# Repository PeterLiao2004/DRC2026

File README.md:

# DRC2026 Autonomous Car

Autonomous car project using a Raspberry Pi 5 for high-level autonomy and a Raspberry Pi Pico for low-level motor control.

## Repository Layout

```text
DRC2026/
+-- pi5_software/       High-level autonomy, perception, planning, and Pi-side services
+-- pico_firmware/      Low-level motor, encoder, and safety firmware for the Raspberry Pi Pico
+-- PCB/                KiCad PCB project, footprints, symbols, and fabrication outputs
+-- interfaces/         Communication contracts between the Pi 5, Pico, and hardware
+-- docs/               System architecture, bring-up notes, and design decisions
```

## System Roles

- **Raspberry Pi 5:** Main computer for camera processing, navigation, decision making, logging, and sending drive commands.
- **Raspberry Pi Pico:** Real-time controller for motors, encoders, watchdogs, and low-level safety behavior.
- **PCB:** Custom carrier/control board that connects power, Pico, motor driver, encoders, and expansion headers.

## Suggested Development Flow

1. Define or update the Pi-to-Pico protocol in `interfaces/`.
2. Implement low-level behavior in `pico_firmware/` and test it on the bench.
3. Implement high-level autonomy in `pi5_software/` against the same protocol.
4. Capture wiring, power, and bring-up notes in `docs/`.
5. Keep PCB source files and generated fabrication outputs in `PCB/`.

## Bring-Up Checklist

- Confirm PCB power rails before connecting the Pi 5 or Pico.
- Flash Pico firmware and verify motor disable/stop behavior first.
- Verify encoder telemetry with the car lifted off the ground.
- Connect Pi 5 software to the Pico protocol and test low-speed commands.
- Add autonomy features only after manual command and safety paths are reliable.

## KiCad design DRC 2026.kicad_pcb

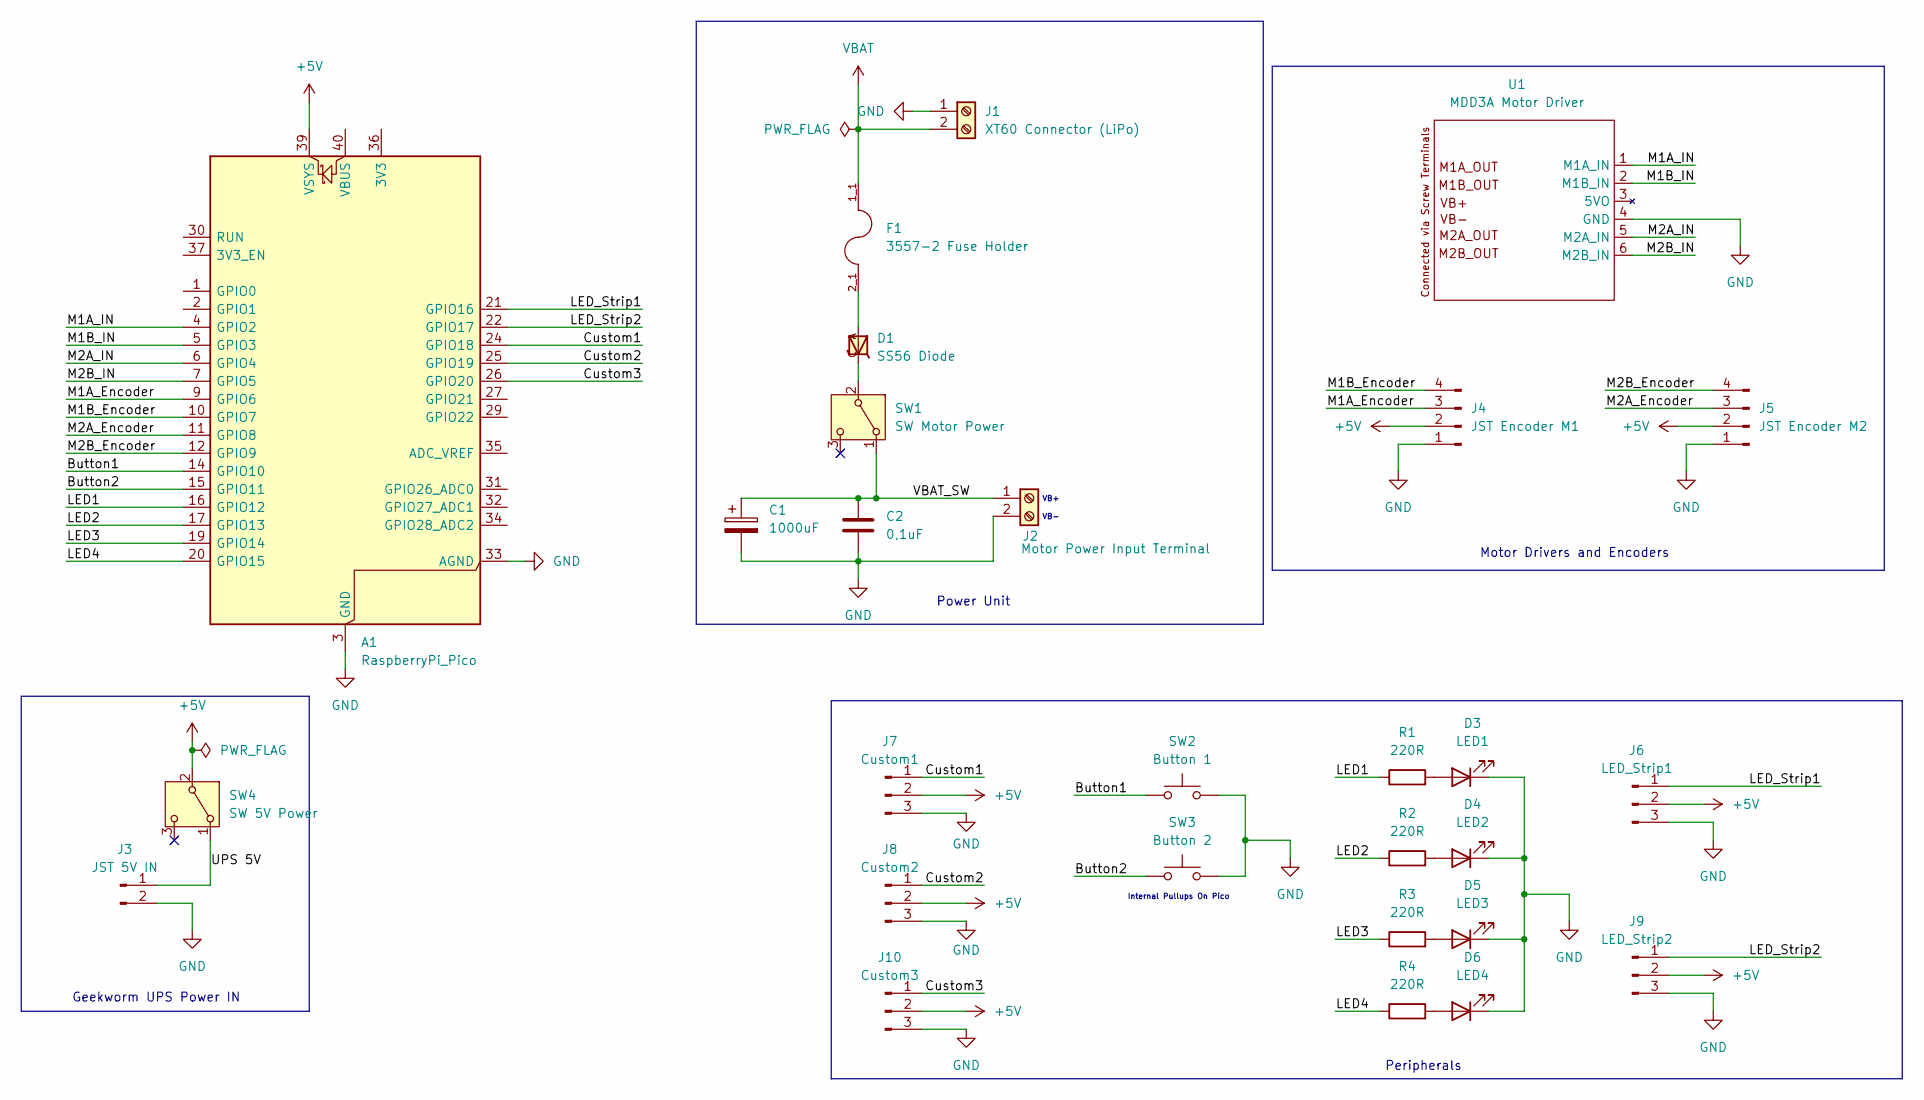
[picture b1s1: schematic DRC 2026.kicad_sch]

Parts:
A1: RaspberryPi_Pico; RaspberryPi_Pico_Dual_Header
C1: 1000uF; Capacitor_35PK1000MEFC10X20
C2: 0,1uF; CAPRR508W54L508T381H660
D1: SS56 Diode
D3: LED1; LED_D5.0mm
D4: LED2; LED_D5.0mm
D5: LED3; LED_D5.0mm
D6: LED4; LED_D5.0mm
F1: 3557-2 Fuse Holder; FUSE_3557-2; PARTREV D
J1: XT60 Connector (LiPo); AMASS_XT60PW-M_1x02_P7.20mm_Horizontal
J2: Motor Power Input Terminal; TerminalBlock_CUI_TB007-508-02_1x02_P5.08mm_Horizontal
J3: JST 5V IN; JST_XH_B2B-XH-A_1x02_P2.50mm_Vertical
J4: JST Encoder M1; JST_XH_B4B-XH-A_1x04_P2.50mm_Vertical
J5: JST Encoder M2; JST_XH_B4B-XH-A_1x04_P2.50mm_Vertical
J6: LED_Strip1; PinHeader_1x03_P2.54mm_Vertical
J7: Custom1; PinHeader_1x03_P2.54mm_Vertical
J8: Custom2; PinHeader_1x03_P2.54mm_Vertical
J9: LED_Strip2; PinHeader_1x03_P2.54mm_Vertical
J10: Custom3; PinHeader_1x03_P2.54mm_Vertical
R1, R2, R3, R4: 220R; R_0805_2012Metric_Pad1.20x1.40mm_HandSolder
SW1: SW Motor Power; SW_500SSP1S2M2QEA
SW2: Button 1; SW_PUSH_6mm
SW3: Button 2; SW_PUSH_6mm
SW4: SW 5V Power; SW_500SSP1S2M2QEA
U1: MDD3A Motor Driver

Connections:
+5V: A1.39 (VSYS), J4.2, J5.2, J6.2, J7.2, J8.2, J9.2, J10.2, SW4.2 (B)
/Button1: A1.14 (GPIO10), SW2.1
/Button2: A1.15 (GPIO11), SW3.1
/Custom1: A1.24 (GPIO18), J7.1
/Custom2: A1.25 (GPIO19), J8.1
/Custom3: A1.26 (GPIO20), J10.1
/LED1: A1.16 (GPIO12), R1.1
/LED2: A1.17 (GPIO13), R2.1
/LED3: A1.19 (GPIO14), R3.1
/LED4: A1.20 (GPIO15), R4.1
/LED_Strip1: A1.21 (GPIO16), J6.1
/LED_Strip2: A1.22 (GPIO17), J9.1
/M1A_Encoder: A1.9 (GPIO6), J4.3
/M1A_IN: A1.4 (GPIO2), U1.1 (M1A_IN)
/M1B_Encoder: A1.10 (GPIO7), J4.4
/M1B_IN: A1.5 (GPIO3), U1.2 (M1B_IN)
/M2A_Encoder: A1.11 (GPIO8), J5.3
/M2A_IN: A1.6 (GPIO4), U1.5 (M2A_IN)
/M2B_Encoder: A1.12 (GPIO9), J5.4
/M2B_IN: A1.7 (GPIO5), U1.6 (M2B_IN)
/UPS 5V: J3.1, SW4.1 (A)
/VBAT_SW: C1.1, C2.1, J2.1, SW1.1 (A); also elsewhere on the board
GND: A1.3 (GND), A1.8 (GND), A1.13 (GND), A1.18 (GND), A1.23 (GND), A1.28 (GND), A1.33 (AGND), A1.38 (GND), C1.2, C2.2, D3.1 (K), D4.1 (K), D5.1 (K), D6.1 (K), J1.1, J2.2, J3.2, J4.1, J5.1, J6.3, J7.3, J8.3, J9.3, J10.3, SW2.2, SW3.2, U1.4 (GND); also elsewhere on the board
unnamed: D1.A, F1.2_1, F1.2_2
unnamed: D3.2 (A), R1.2
unnamed: D4.2 (A), R2.2
unnamed: D5.2 (A), R3.2
unnamed: D6.2 (A), R4.2
unnamed 28: D1.C, SW1.2 (B); also elsewhere on the board
VBAT: F1.1_1, F1.1_2, J1.2; also elsewhere on the board

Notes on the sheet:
Power Unit
VB-
Internal Pullups On Pico
Peripherals
Geekworm UPS Power IN
VB+
Motor Drivers and Encoders

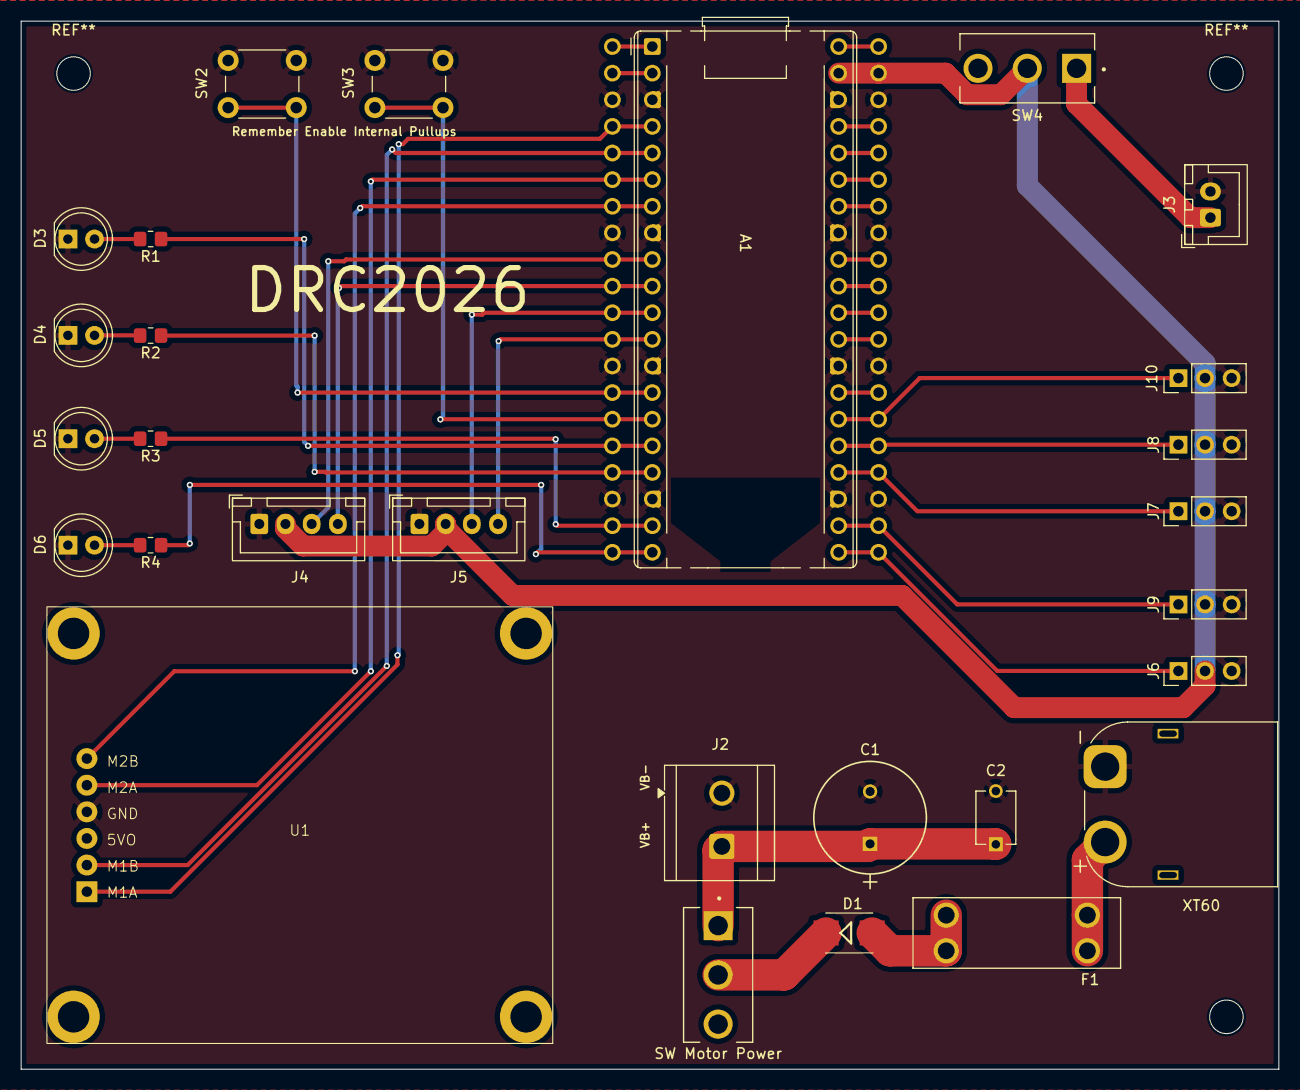
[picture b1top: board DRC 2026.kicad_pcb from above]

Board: 2 copper layers, 120.0 x 100.0 mm, 28 parts (0 on the bottom side), 30 nets.

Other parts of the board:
SW Motor Power: SW Motor Power; SW_500SSP1S2M2QEA
XT60: XT60 Connector (LiPo); AMASS_XT60PW-M_1x02_P7.20mm_Horizontal

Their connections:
/VBAT_SW: SW Motor Power.1 (A); also elsewhere on the board
GND: XT60.1; also elsewhere on the board
unnamed 28: SW Motor Power.2 (B); also elsewhere on the board
VBAT: XT60.2; also elsewhere on the board

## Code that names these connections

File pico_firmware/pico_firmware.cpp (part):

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#define M2_ENCODER_B 9

//Buttons
#define BUTTON1 10
#define BUTTON2 11

//LED Pins
#define LED1 12
#define LED2 13
#define LED3 14
#define LED4 15
#define STATUS_LED_PIN PICO_DEFAULT_LED_PIN

//LED Strip Pins
#define LED_STRIP1 16
#define LED_STRIP2 17
#define LED_STRIP1_COUNT 43
#define LED_STRIP_BRIGHTNESS 32
#define LED_STRIP_FRAME_MS 30

//Custom Pins (for future use, e.g. sensors)
#define CUSTOM1 18
#define CUSTOM2 19
#define CUSTOM3 20
//--------------------Control Parameters------------------//
// PWM settings
#define PWM_WRAP 1000
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    setup_encoders();

    // Buttons are active-low: pressed reads 0, released reads 1.
    const uint button_pins[] = {BUTTON1, BUTTON2};
    for (uint pin : button_pins) {
        gpio_init(pin);
        gpio_set_dir(pin, GPIO_IN);
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    }

    // Status LEDs start switched off.
    const uint led_pins[] = {LED1, LED2, LED3, LED4, STATUS_LED_PIN};
    for (uint pin : led_pins) {
        gpio_init(pin);
        gpio_set_dir(pin, GPIO_OUT);
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    }

    // Hold the LED-strip data pins low until strip control is implemented.
    const uint led_strip_pins[] = {LED_STRIP1, LED_STRIP2};
    for (uint pin : led_strip_pins) {
        gpio_init(pin);
        gpio_set_dir(pin, GPIO_OUT);
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    }

    // Leave future-use pins as high-impedance inputs.
    const uint custom_pins[] = {CUSTOM1, CUSTOM2, CUSTOM3};
    for (uint pin : custom_pins) {
        gpio_init(pin);
        gpio_set_dir(pin, GPIO_IN);
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}

void set_all_leds(bool on) {
    const uint led_pins[] = {LED1, LED2, LED3, LED4, STATUS_LED_PIN};
    for (uint pin : led_pins) {
        set_led(pin, on);
    }
}

void run_led_test() {
    const uint led_pins[] = {LED1, LED2, LED3, LED4, STATUS_LED_PIN};

    printf("\nLED test: each LED should light in sequence.\n");
    set_all_leds(false);
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
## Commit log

2026-02-17 Initial commit - schematic + pcb base
2026-02-17 Add README for DRC Robot PCB project
    Added detailed project overview and specifications for DRC Robot PCB.
2026-02-17 Revise README for DRC Robot PCB
    Updated README to improve clarity and structure, including a new usage section with cloning instructions.
2026-06-18 Changed folder structure
2026-06-18 Updated Folder structure
2026-06-18 Pico Firmware SDK setup
2026-06-18 Workspace setup
2026-06-19 Basic motor control
2026-06-19 Basic motor PWM control
2026-06-19 Basic motor driving demo
2026-06-20 Basic motor movement with encoder readings
2026-06-22 Create thresholding app for picam
2026-06-22 PICO: Updated motor control defines
2026-06-22 PICO: comments
2026-06-22 PICO: Test encoder counts.
2026-06-22 PICO: more comments, motor drive test
2026-06-22 PICO: keyboard drive
2026-06-22 PICO: keyboard drive direction fixed
2026-06-22 PICO: motor direction change
2026-06-22 Add final value outputs
2026-06-22 Add code to find lines and calculate centre error
2026-06-22 PICO: keyboard drive direction fix
2026-06-22 Added serial test code (UNTESTED)
2026-06-22 PICO: corrected motor direction
2026-06-22 PICO: simple P control
2026-06-22 PICO: Draft, serial control
2026-06-22 PICO: P control movement done
2026-06-22 GPIO definitions
2026-06-22 PICO: Draft, GPIO setup
2026-06-22 PICO: GPIO testing code
2026-06-23 PICO: GPIO testing code done
2026-06-23 PICO: Drive and Turning LEDs
2026-06-23 Sends serial commands to pico
2026-06-23 PICO: keyboard control
2026-06-23 Tuned thresholds for SL house, adjusted cam settings in threshold app
2026-06-23 PICO: Left/Right error correction. Negative = Left, Positive = Right
2026-06-23 Fixed thresholds, changed serial output
2026-06-23 PICO: speed adjustment
2026-06-23 Added black threshold
2026-06-23 Added arrow detection code (UNTESTED)
2026-06-23 PICO: Speed reduction kinda working
2026-06-23 Arrow detection working (with bounding boxes, points, confidence)
2026-06-23 PICO: KP and KD
2026-06-23 Arrow detection working, line following working
2026-06-23 Arrow detection removed extra outputs
2026-06-23 Added merged line and arrow code, still buggy
2026-06-23 Strengthen arrow detection
2026-06-23 Arrows still need tuning, stops on green!
2026-06-23 Changed cam settings for uni lighting
2026-06-23 Lines at uni, arrow slow and confirm, PID serial
2026-06-23 Green follows line, arrow better not perfect, PID tuned with shell
2026-06-23 Threshold app takes inputs
2026-06-23 Fixed thresholds
2026-06-23 Avoids obstacles!
2026-06-23 Adjusting arrow numbers
2026-06-24 Mapping function
2026-06-24 PICO: Adjusted KP and KD again
2026-06-24 PICO: PI5 adjusts PID
2026-06-24 PICO: RPM test
2026-06-24 PICO: RPM measurement with encoders
2026-06-24 PICO: cleanup, remove keyboard control
2026-06-24 PICO: RPM readings
2026-06-24 RPM read rate update
2026-06-24 RPM: Not working
2026-06-24 PICO: Closed loop control seems to work
2026-06-24 PICO: closed loop control works
2026-06-24 Kinda working code - track from @1:30
2026-06-24 Serial test for speed
2026-06-24 Code working decent, adjusted camera band lower (fixed corner cutting)
2026-06-24 CODE WORKING (pretty well) - fixed obstacle avoidance)
2026-06-24 Various speed options
2026-06-24 Changing vals
2026-06-24 Tuned thresholds (yellow)
2026-06-26 PICO: LED lights up
2026-06-26 PICO: LED Animations
